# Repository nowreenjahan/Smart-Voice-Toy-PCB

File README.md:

# FunLearnLab: Smart Voice Learning Toy Main Board

## 1. Project Overview & System Requirements
Designed and engineered a production-ready, compact 2-layer main PCB for an offline-focused smart educational toy targeted at children aged 3–6

### Key Constraints & Requirements:
* **Form Factor:** Compact design constrained to 6cm x 6cm or 8cm x 8cm to seamlessly fit the toy enclosure.
* **Layer Count:** 4-Layer stackup implemented to preserve signal integrity, enhance Wi-Fi performance, stabilize camera feeds, and minimize audio noise.
* **Primary Processing:** ESP32-S3 microcontroller utilizing built-in Wi-Fi/Bluetooth, external flash/SD storage, and an external Audio Codec for offline voice processing.
* **Peripherals Controlled:** 3W/5W Speaker (Class-D Amp), MEMS Microphone, OV2640 Camera Module, Small LED Matrix/IPS Face Display, Dual DC Wheel Motors (DRV8833/L9110), and Physical Buttons.

## 2. Component Selection & Schematic Design
* **Processor Core:** Deployed the ESP32-S3 and integrated high-capacity flash storage to house local voice lessons, audio files, and LED animation profiles offline.
* **Audio Subsystem:** Combined a high-fidelity MEMS microphone for child voice pickup with a MAX98357A Class-D Audio Amplifier to drive the speaker efficiently without generating heavy thermal waste.
* **Motor Driver:** Used an H-bridge IC (L9110/DRV8833) to handle the dual side-wheel steering motors, ensuring the control lines were heavily decoupled from the logic power rails.

## 3. Custom Library Generation
* **Fine-Pitch Connectors:** Drafted custom FPC connector footprints for the OV2640 Camera and LED Display, ensuring tight pad tolerances to avoid solder bridging during automated assembly (PCBA).

## 4. PCB Layout & Routing Strategy
* **Noise Isolation:** Explicitly isolated the motor driver routing and high-current motor power traces away from the sensitive analog lines of the audio amplifier and MEMS microphone to prevent audible buzzing or distortion during toy movement.
* **Thermal Management:** Implemented thermal vias and solid copper pours underneath the camera zone to dissipate heat generated during continuous video processing.

## 5. Repository Structure
* `01_PCB_Requirements_English.md`: Full English translation of the design requirement sheet for cross-border manufacturing compatibility.
* `02_Schematics/`: Complete schematic sheets in PDF format.
* `03_Custom_Libraries/`: Custom footprint folders, symbols, and STEP models.
* `04_PCB_Layout_Designs/`: 2D/3D design layout assets.
* `05_Manufacturing/`: Production-ready Gerbers, Drill files, BOM, and CPL files.
* `06_Images/`: Project screenshots and 3D rendering profiles.

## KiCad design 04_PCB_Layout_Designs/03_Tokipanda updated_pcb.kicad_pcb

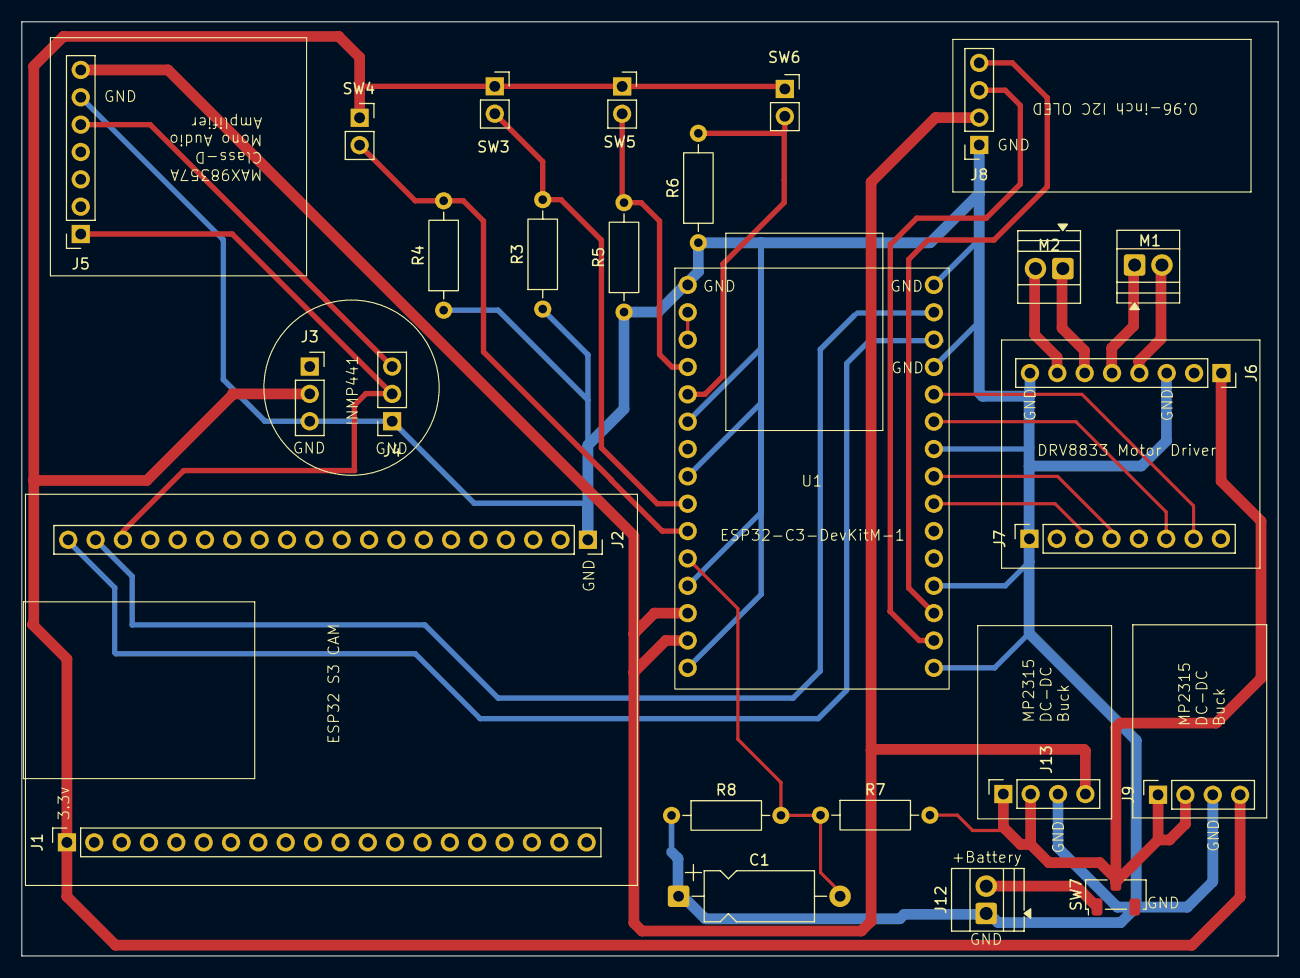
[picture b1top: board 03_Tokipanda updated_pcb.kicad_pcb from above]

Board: 2 copper layers, 116.7 x 86.8 mm, 26 parts (0 on the bottom side), 24 nets.

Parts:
C1: 0.001mF; CP_Axial_L10.0mm_D4.5mm_P15.00mm_Horizontal
J1, J2: Conn_01x20_MountingPin; PinSocket_1x20_P2.54mm_Vertical
J3, J4: Conn_01x03; PinSocket_1x03_P2.54mm_Vertical
J5: Conn_01x07; PinSocket_1x07_P2.54mm_Vertical
J6, J7: Conn_01x08; PinSocket_1x08_P2.54mm_Vertical
J8, J9, J13: Conn_01x04; PinSocket_1x04_P2.54mm_Vertical
J12: Conn_01x02; TerminalBlock_Xinya_XY308-2.54-2P_1x02_P2.54mm_Horizontal
M1, M2: Motor_DC; TerminalBlock_Xinya_XY308-2.54-2P_1x02_P2.54mm_Horizontal
R3, R4, R5, R6: 10k; R_Axial_DIN0207_L6.3mm_D2.5mm_P10.16mm_Horizontal
R7: 100k; R_Axial_DIN0207_L6.3mm_D2.5mm_P10.16mm_Horizontal
R8: 47k; R_Axial_DIN0207_L6.3mm_D2.5mm_P10.16mm_Horizontal
SW3, SW4, SW5, SW6: SW_Push; PinSocket_1x02_P2.54mm_Vertical
SW7: SW_Nidec_CAS-120A1; Nidec_Copal_CAS-120A
U1: ESP32-C3-DevKitM-1; ESP32_C3_headers

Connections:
3v3: J1.1 (Pin_1_1), J3.2, J9.4, SW3.1, SW4.1, SW5.1, SW6.1
5v: J5.7, J8.2, J13.4, U1.13 (5V), U1.14 (5V)
7v4: J12.2, SW7.1 (C)
GND: C1.1, J2.1, J3.3, J4.1, J5.6, J6.3, J6.8, J7.1, J8.1, J9.3, J12.1, J13.3, R3.1, R4.1, R5.1, R6.1, R8.1, SW7.3 (A), U1.1 (GND), U1.6 (GND), U1.8 (GND), U1.12 (GND), U1.15 (GND), U1.16 (GND), U1.19 (GND), U1.24 (GND), U1.27 (GND), U1.30 (GND)
NC: J5.2, J5.4
unnamed: J4.3, J5.5
unnamed: J6.4, M1.2 (-)
unnamed: J6.5, M1.1 (+)
unnamed: J6.6, M2.1 (+)
unnamed: J6.7, M2.2 (-)
unnamed: J7.3, U1.23 (IO7)
unnamed: J7.4, U1.22 (IO6)
unnamed: J7.6, U1.21 (IO5)
unnamed: J7.7, U1.20 (IO4)
unnamed: J8.3, U1.17 (IO19)
unnamed: J8.4, U1.18 (IO18)
unnamed: U1.2 (3V3), U1.3 (3V3)
unnamed: R3.2, SW3.2, U1.9 (IO0)
unnamed: R4.2, SW4.2, U1.10 (IO1)
unnamed: R5.2, SW5.2, U1.4 (IO2)
unnamed: R6.2, SW6.2, U1.5 (IO3)
unnamed: C1.2, R7.1, R8.2, U1.11 (IO10)
SW_On: J6.1, J9.1, J9.2, J13.1, J13.2, R7.2, SW7.2 (B)
WS: J4.2, J5.1

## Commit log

2026-06-09 README.md
